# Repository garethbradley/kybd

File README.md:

# Maizeglow Keyboard
Config and design for custom split keyboard

config.yaml is for use by ergogen (https://ergogen.ceoloide.com/)

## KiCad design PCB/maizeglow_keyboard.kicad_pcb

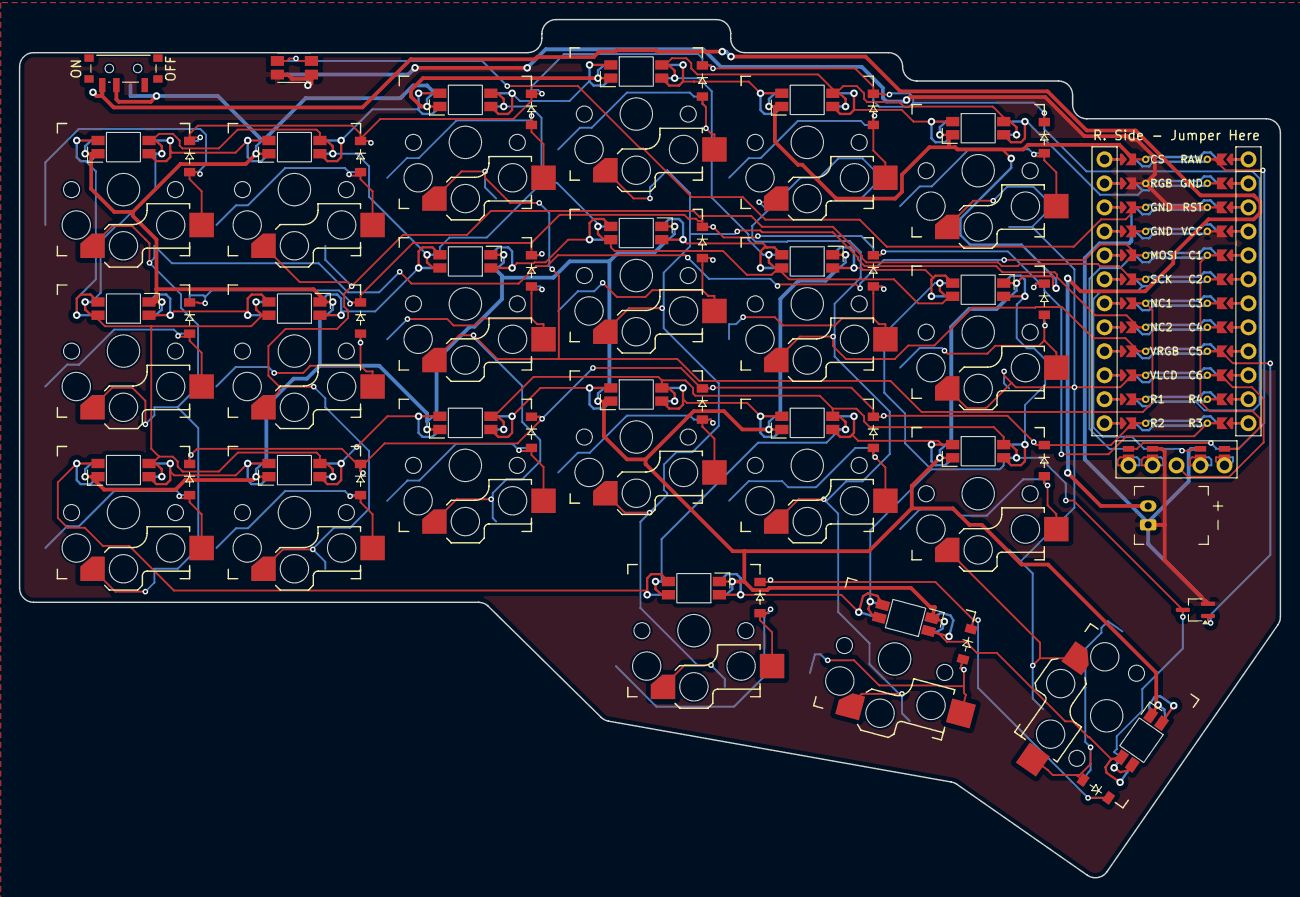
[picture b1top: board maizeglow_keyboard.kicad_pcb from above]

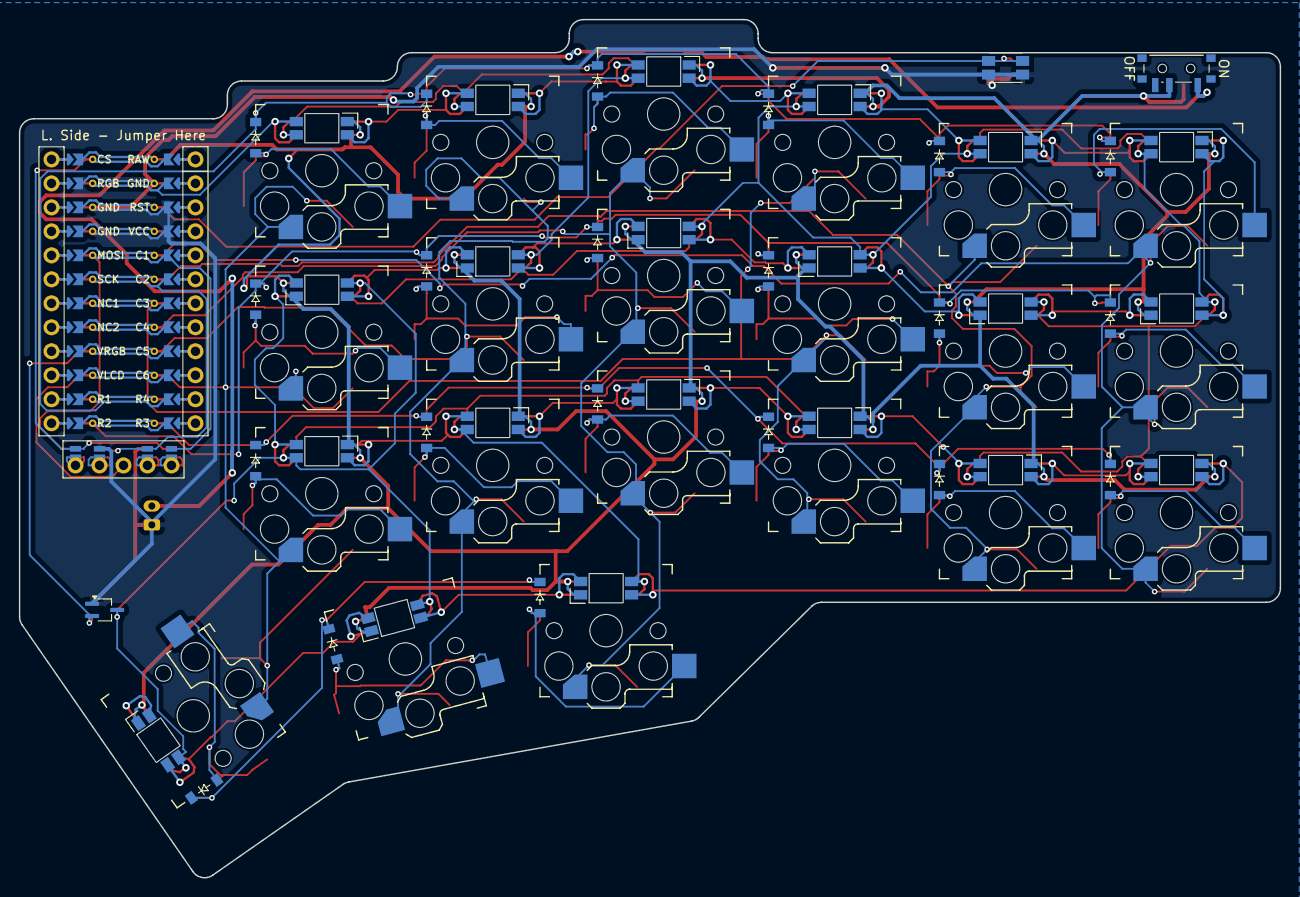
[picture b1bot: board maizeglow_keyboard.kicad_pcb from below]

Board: 2 copper layers, 133.5 x 90.9 mm, 69 parts (23 on the bottom side), 66 nets.

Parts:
D1, D2, D3, D4, D5, D6, D7, D8, D9, D10, D11, D12, D13, D14, D15, D16, D17, D18, D19, D20, D21: ComboDiode
D22: mosfet_pjc7400
DISP1: nice!view
JST1: battery_connector_jst_ph_2
LED1, LED2, LED3, LED4, LED5, LED6, LED7, LED8, LED9, LED10, LED11, LED12, LED13, LED14, LED15, LED16, LED17, LED18, LED19, LED20, LED21: led_SK6812mini-e (per-key, reversible)
MCU1: nice_nano
PWR1: power_switch_smd_side
S1, S2, S3, S4, S5, S6, S7, S8, S9, S10, S11, S12, S13, S14, S15, S16, S17, S18, S19, S20, S21: PG1350
SW1: sw_reset_side

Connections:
BAT_P: JST1.2, PWR1.1, PWR1.3
C1: MCU1.120, S2.1, S3.1, S4.1
C2: MCU1.119, S5.1, S6.1, S7.1
C3: MCU1.118, S8.1, S9.1, S10.1
C4: MCU1.117, S11.1, S12.1, S13.1, S20.1
C5: MCU1.116, S14.1, S15.1, S16.1, S21.1
C6: MCU1.115, S1.1, S17.1, S18.1, S19.1
CS: DISP1.14, DISP1.24, MCU1.1
DISP1_1: DISP1.1, DISP1.10, DISP1.23
DISP1_2: DISP1.2, DISP1.11, DISP1.22
DISP1_4: DISP1.4, DISP1.12, DISP1.21
DISP1_5: DISP1.5, DISP1.13, DISP1.20
GND: D22.1, D22.2, DISP1.15, DISP1.25, JST1.1, MCU1.3, MCU1.4, MCU1.123, SW1.1
LED_DRAIN: D22.3, LED1.1, LED2.1, LED3.1, LED4.1, LED5.1, LED6.1, LED7.1, LED8.1, LED9.1, LED10.1, LED11.1, LED12.1, LED13.1, LED14.1, LED15.1, LED16.1, LED17.1, LED18.1, LED19.1, LED20.1, LED21.1
MOSI: DISP1.17, DISP1.27, MCU1.5
P010: D19.1, D20.1, D21.1
R1: D3.1, D6.1, D9.1, D12.1, D15.1, D18.1, MCU1.11
R2: D2.1, D5.1, D8.1, D11.1, D14.1, D17.1, MCU1.12
R3: D1.1, D4.1, D7.1, D10.1, D13.1, D16.1, MCU1.113
RAW: LED1.3, LED2.3, LED3.3, LED4.3, LED5.3, LED6.3, LED7.3, LED8.3, LED9.3, LED10.3, LED11.3, LED12.3, LED13.3, LED14.3, LED15.3, LED16.3, LED17.3, LED18.3, LED19.3, LED20.3, LED21.3, MCU1.124, PWR1.2
RGB: LED1.2, MCU1.2
RGB_2: LED1.4, LED2.2
RGB_3: LED2.4, LED3.2
RGB_4: LED3.4, LED4.2
RGB_5: LED4.4, LED5.2
RGB_6: LED5.4, LED6.2
RGB_7: LED6.4, LED7.2
RGB_8: LED7.4, LED8.2
RGB_9: LED8.4, LED9.2
RGB_10: LED9.4, LED10.2
RGB_11: LED10.4, LED11.2
RGB_12: LED11.4, LED12.2
RGB_13: LED12.4, LED13.2
RGB_14: LED13.4, LED14.2
RGB_15: LED14.4, LED15.2
RGB_16: LED15.4, LED16.2
RGB_17: LED16.4, LED17.2
RGB_18: LED17.4, LED18.2
RGB_19: LED18.4, LED19.2
RGB_20: LED19.4, LED20.2
RGB_21: LED20.4, LED21.2
RST: MCU1.122, SW1.2
SCK: DISP1.16, DISP1.26, MCU1.6
VLCD: DISP1.3, MCU1.10
VRGB: D22.1, D22.2, MCU1.9
far_thumb: D21.2, S1.2
home_thumb: D20.2, S21.2
index_bottom: D13.2, S14.2
index_middle: D14.2, S15.2
index_top: D15.2, S16.2
inner_bottom: D16.2, S17.2
inner_middle: D17.2, S18.2
inner_top: D18.2, S19.2
macro_bottom: D1.2, S2.2
macro_middle: D2.2, S3.2
macro_top: D3.2, S4.2
middle_bottom: D10.2, S11.2
middle_middle: D11.2, S12.2
middle_top: D12.2, S13.2
near_thumb: D19.2, S20.2
pinky_bottom: D4.2, S5.2
pinky_middle: D5.2, S6.2
pinky_top: D6.2, S7.2
ring_bottom: D7.2, S8.2
ring_middle: D8.2, S9.2
ring_top: D9.2, S10.2

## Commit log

2024-10-11 Updated board outline
2024-10-11 Started PCB design
2024-10-11 Fix board outline above matrix_middle_num
2024-10-12 Added diodes
2024-10-14 progress...
2024-10-15 Change to 3x6 layout with 3 thumb keys
2024-10-16 Replacing infused-kim with forked version
2024-10-17 Finalised board shape
2024-10-17 Added LEDs
2024-10-22 Board template complete. Started PCB Routing
2024-11-11 Working without power domains
2024-12-05 Change repo name to reflect maizeglow
